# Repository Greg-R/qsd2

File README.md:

QSD2 Receiver Module

The documentation for this design is located here:
<https://kf5n.com/t41-2/qsd2ez/>

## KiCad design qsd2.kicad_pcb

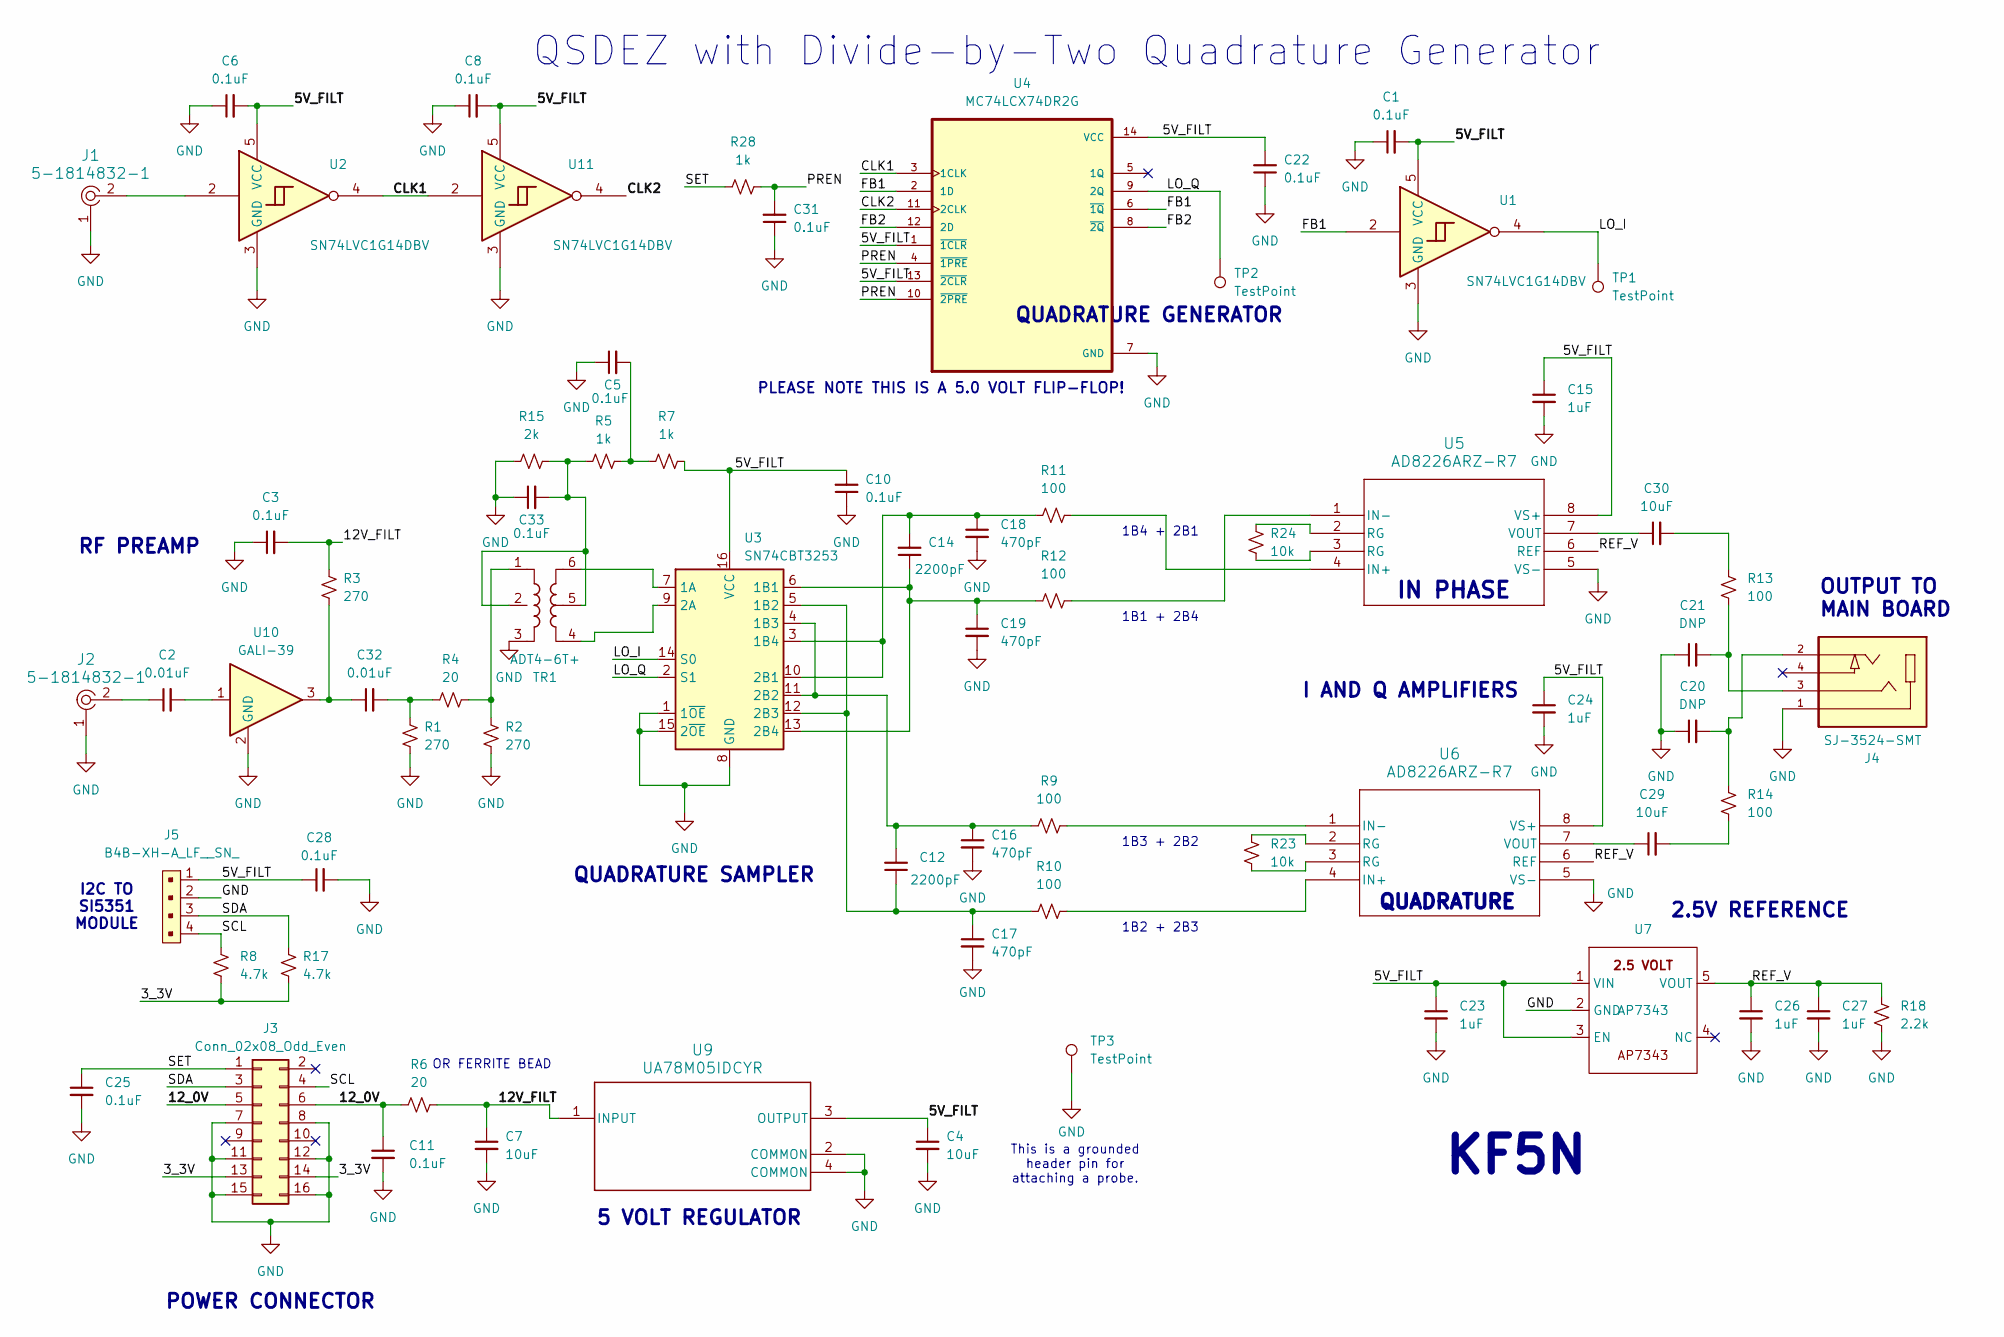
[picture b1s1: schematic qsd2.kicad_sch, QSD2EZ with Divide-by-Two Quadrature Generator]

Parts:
C1, C3, C5, C6, C8, C10, C11, C22, C25, C28, C31, C33: 0.1uF; C_1206_3216Metric
C2, C32: 0.01uF; C_1206_3216Metric
C4, C7, C29, C30: 10uF; C_1206_3216Metric
C12, C14: 2200pF; C_1206_3216Metric
C15, C23, C24, C26, C27: 1uF; C_1206_3216Metric
C16, C17, C18, C19: 470pF; C_1206_3216Metric
C20, C21: DNP; C_1206_3216Metric
J1, J2: 5-1814832-1; RF_SMA_Vertical_5-1814832-1; MPN 5-1814832-1; Digi-Key_PN A97594-ND
J3: Conn_02x08_Odd_Even; IDC-Header_2x08_P2.54mm_Vertical
J4: SJ-3524-SMT; CUI_SJ-3524-SMT; PARTREV 1.03
J5: B4B-XH-A_LF__SN_; PinHeader_1x4_P2.5mm_Drill1.1mm; MPN B4B-XH-A(LF)(SN); Digi-Key_PN 455-2249-ND
R1, R2, R3: 270; R_1206_3216Metric
R4, R6: 20; R_1206_3216Metric
R5, R7, R28: 1k; R_1206_3216Metric
R8, R17: 4.7k; R_1206_3216Metric
R9, R10, R11, R12, R13, R14: 100; R_1206_3216Metric
R15: 2k; R_1206_3216Metric
R18: 2.2k; R_1206_3216Metric
R23, R24: 10k; R_1206_3216Metric
TP1, TP2: TestPoint; TestPoint_Pad_D1.0mm
TP3: TestPoint; PinHeader_1x01_P2.54mm_Vertical
TR1: ADT4-6T+; Mini-Circuits_CD637_H5.23mm
U1, U2, U11: SN74LVC1G14DBV; SOT-23-5
U3: SN74CBT3253; SOIC-16_3.9x9.9mm_P1.27mm
U4: MC74LCX74DR2G; SOIC-14_3.9x8.7mm_P1.27mm
U5, U6: AD8226ARZ-R7; R_8_ADI
U7: AP7343; SOT-23-5
U9: UA78M05IDCYR; DCY0004A_N
U10: GALI-39; SOT-89-3

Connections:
/3_3V: J3.13, J3.14, R8.2, R17.2
/5V_FILT: C1.2, C4.1, C6.2, C8.2, C10.2, C15.1, C22.2, C23.1, C24.1, C28.1, J5.1, R7.2, U1.5 (VCC), U2.5 (VCC), U3.16 (VCC), U4.1 (~1CLR), U4.13 (~2CLR), U4.14 (VCC), U5.8 (VS+), U6.8 (VS+), U7.1 (VIN), U7.3 (EN), U9.3 (OUTPUT), U11.5 (VCC)
/12V_FILT: C3.2, C7.1, R3.1, R6.2, U9.1 (INPUT)
/12_0V: C11.1, J3.5, J3.6, R6.1
/CLK1: U2.4, U4.3 (1CLK), U11.2
/CLK2: U4.11 (2CLK), U11.4
/FB1: U1.2, U4.2 (1D), U4.6 (~1Q)
/FB2: U4.8 (~2Q), U4.12 (2D)
/LO_I: TP1.1 (1_1), U1.4, U3.14 (S0)
/LO_Q: TP2.1 (1_1), U3.2 (S1), U4.9 (2Q)
/PREN: C31.2, R28.2, U4.4 (~1PRE), U4.10 (~2PRE)
/REF_V: C26.1, C27.1, R18.1, U5.6 (REF), U6.6 (REF), U7.5 (VOUT)
/SCL: J3.4, J5.4, R8.1
/SDA: J3.3, J5.3, R17.1
/SET: C25.1, J3.1, R28.1
GND: C1.1, C3.1, C4.2, C5.1, C6.1, C7.2, C8.1, C10.1, C11.2, C15.2, C16.2, C17.2, C18.2, C19.2, C20.1, C21.1, C22.1, C23.2, C24.2, C25.2, C26.2, C27.2, C28.2, C31.1, C33.1, J1.1, J2.1, J3.7, J3.8, J3.11, J3.12, J3.15, J3.16, J4.1, J5.2, R1.2, R2.2, R15.1, R18.2, TP3.1 (1_1), TR1.3, U1.3 (GND), U2.3 (GND), U3.1 (1~OE), U3.8 (GND), U3.15 (2~OE), U4.7 (GND), U5.5 (VS-), U6.5 (VS-), U7.2 (GND), U9.2 (COMMON), U9.4 (COMMON), U10.2 (GND_2), U11.3 (GND)
unnamed: C2.1, J2.2
unnamed: C2.2, U10.1
unnamed: C5.2, R5.2, R7.1
unnamed: C20.2, J4.2, R14.2
unnamed: C21.2, J4.3, R13.1
unnamed: C29.2, R14.1
unnamed: C30.2, R13.2
unnamed: C32.1, R3.2, U10.3
unnamed: C32.2, R1.1, R4.1
unnamed: C33.2, R5.1, R15.2, TR1.2, TR1.5
unnamed: J1.2, U2.2
unnamed: R2.1, R4.2, TR1.1
unnamed: R23.1, U6.3 (RG)
unnamed: R23.2, U6.2 (RG)
unnamed: R24.1, U5.2 (RG)
unnamed: R24.2, U5.3 (RG)
unnamed: TR1.6, U3.7 (1A)
unnamed: C14.1, C19.1, R12.1, U3.6 (1B1), U3.13 (2B4)
unnamed: C12.1, C17.1, R10.1, U3.5 (1B2), U3.12 (2B3)
unnamed: C12.2, C16.1, R9.1, U3.4 (1B3), U3.11 (2B2)
unnamed: C14.2, C18.1, R11.1, U3.3 (1B4), U3.10 (2B1)
unnamed: TR1.4, U3.9 (2A)
unnamed: R11.2, U5.4 (IN+)
unnamed: R12.2, U5.1 (IN-)
unnamed: C30.1, U5.7 (VOUT)
unnamed: R10.2, U6.4 (IN+)
unnamed: R9.2, U6.1 (IN-)
unnamed: C29.1, U6.7 (VOUT)

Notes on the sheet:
KF5N
2.5V REFERENCE
OR FERRITE BEAD
5 VOLT REGULATOR
1B2 + 2B3
This is a grounded header pin for attaching a probe.
1B3 + 2B2
QUADRATURE
IN PHASE
QUADRATURE SAMPLER
PLEASE NOTE THIS IS A 5.0 VOLT FLIP-FLOP!
QUADRATURE GENERATOR
POWER CONNECTOR
RF PREAMP
1B4 + 2B1
OUTPUT TO MAIN BOARD
I AND Q AMPLIFIERS
1B1 + 2B4
I2C TO SI5351 MODULE
QSDEZ with Divide-by-Two Quadrature Generator

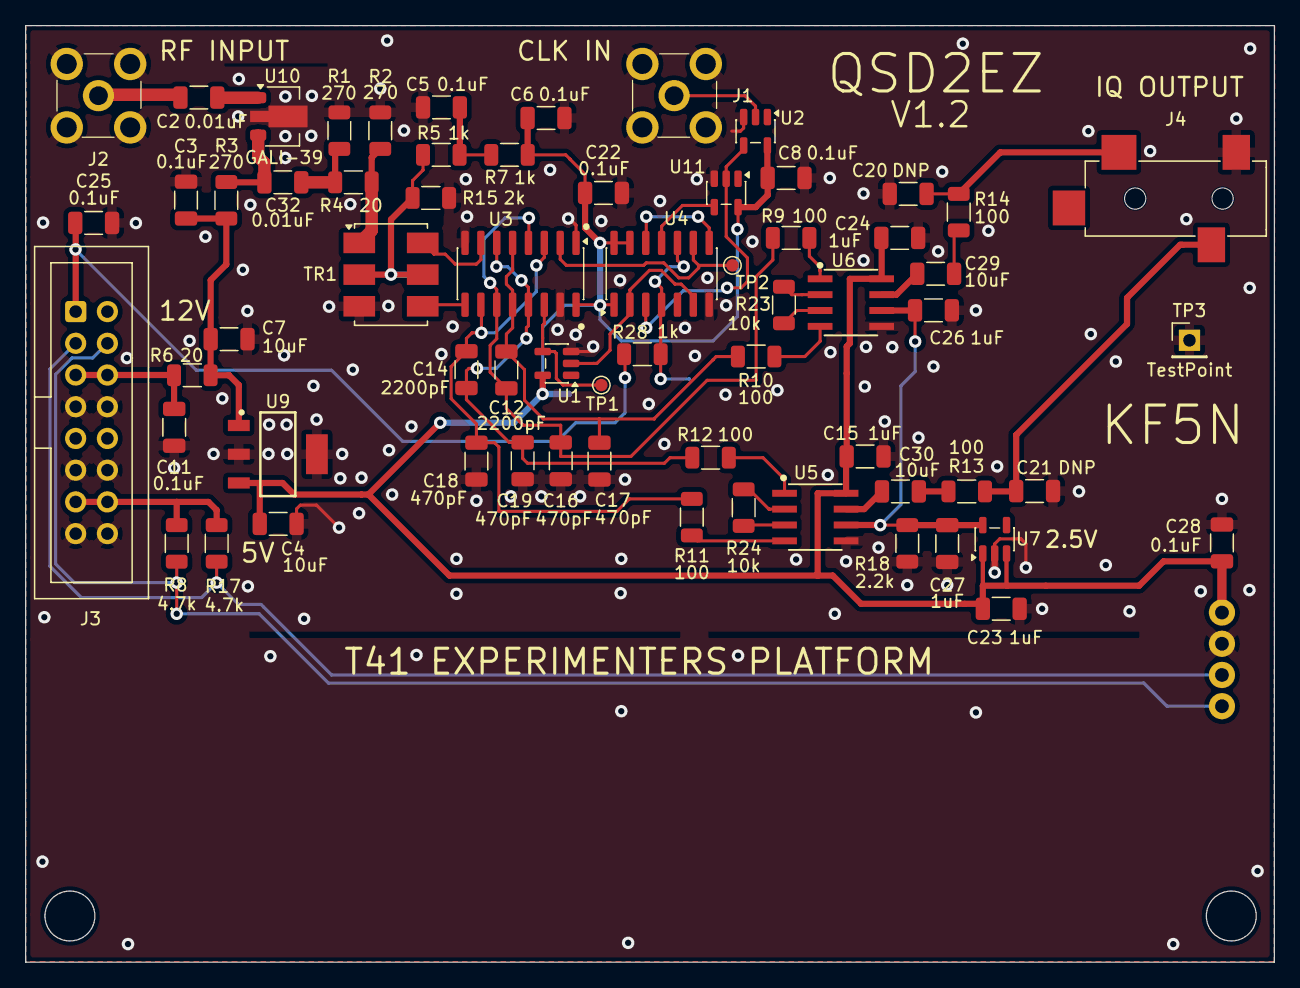
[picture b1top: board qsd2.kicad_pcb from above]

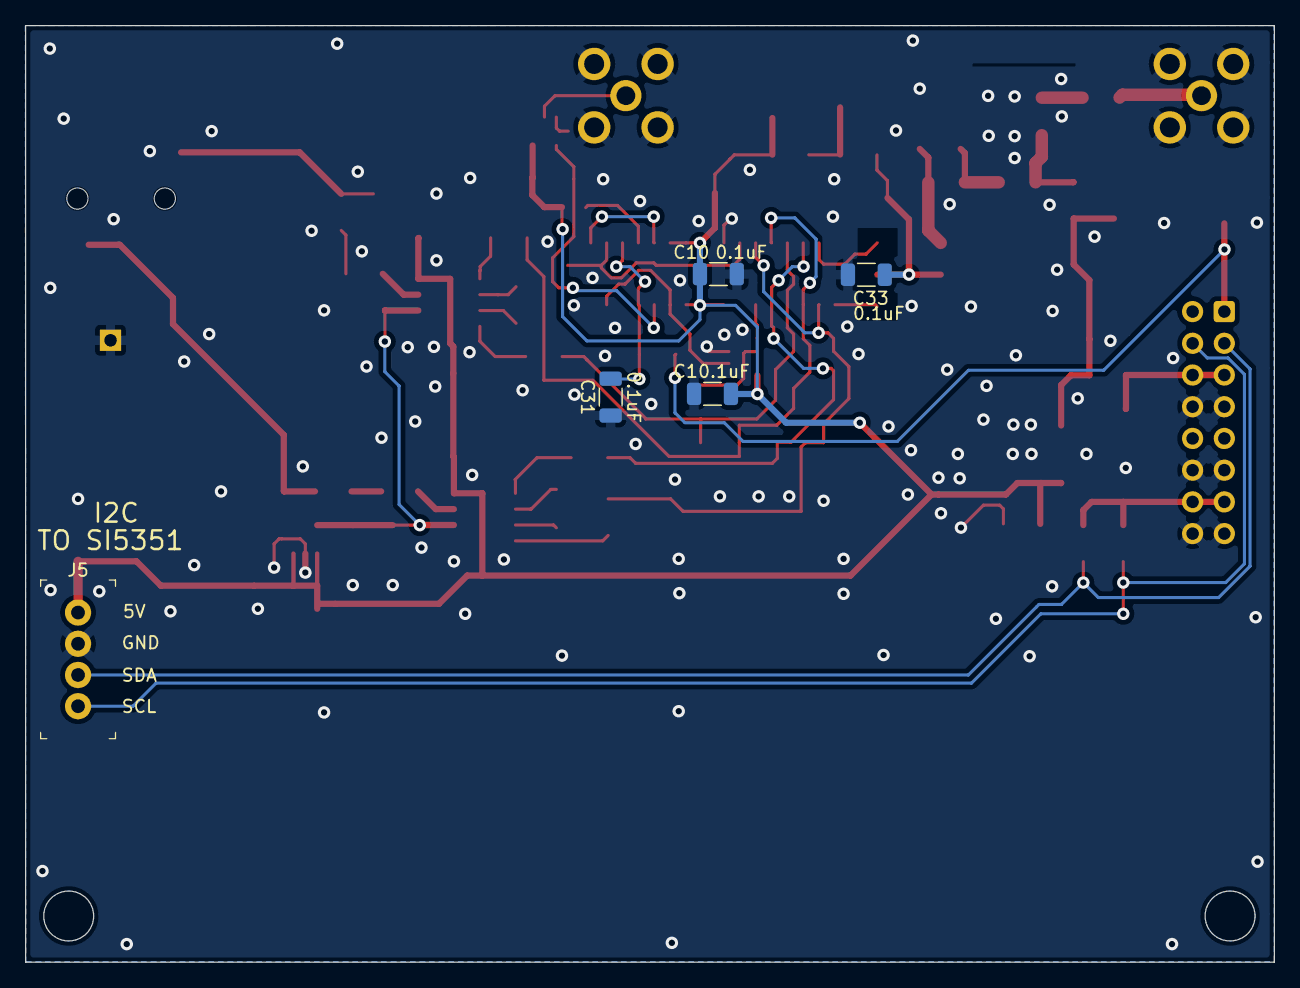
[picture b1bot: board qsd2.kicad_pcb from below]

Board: 2 copper layers, 100.0 x 75.0 mm, 70 parts (5 on the bottom side), 44 nets.

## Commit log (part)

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2023-10-19 Initial commit.
2023-10-19 Changed revision to 1.0.
2023-10-27 Added .gitignore file.
2023-10-27 Major update of the README.md file.
2023-10-27 Minor update of the README.md file.
2023-10-27 Added PDF of schematic.
2023-10-27 Minor update to README.md.
2023-10-27 Removed a zip file.
2023-10-27 Modified gitignore
2023-10-27 Removed spec_sheets.
2023-10-27 Removed backups.
2023-10-27 Updated .gitignore.
2023-10-27 Modified .gitignore.
2023-10-27 Removed qsd2-backups
2023-10-27 Removed spec_sheets
2023-10-28 Did not required downloaded library parts file.
2023-10-28 Added link to public Digikey BOM.
2023-10-28 Minor updates to schematic.
2023-10-28 Added note on calibration.
2023-11-05 Updated README.md with build details.
2023-11-05 Very minor change to silkscreen. Two capacitors 3300pF to 2200pF.
2023-11-06 Added photo of the Main board reset wire.
2023-11-17 Added README.md.
2023-11-18 Updated to version 1.1 PCB. Very minor changes.
2023-11-18 Updated schematic PDF file.
2024-02-19 Mostly done rotating flip-flop and detector.
2024-02-20 Gerbers done, ready to release V1.1.
2024-02-20 Minor clean-up of a few vias.
2024-02-29 Ready to publish version 1.1.
2024-03-03 Removed gerber archive from repository.
2024-04-22 Updated link to the book.
2024-04-22 Updated link to book in README.
2024-04-28 QSD2EZ to V1.0 fab.
2024-04-29 QSD2EZ with lower connector V1.0 to fab.
2024-04-29 Added ZIP file of gerbers.
2024-05-06 Adjusted resistor value position.
2024-05-07 Moved resistor value to more logical location.
2024-05-07 Updated README and BOM for QSD2EZ.
2024-05-07 Minor update to README.
2024-05-07 Updated README.
2024-05-07 Minor change to schematic part number.
2025-07-02 Updated to new version Kicad.
2026-03-11 Updated Kicad version files.
2026-05-20 Added 4 pin connector with 5V and I2C for Si5351 module.
2026-05-21 Ready for fab QSD2EZ V1.1 May 21, 2026.
